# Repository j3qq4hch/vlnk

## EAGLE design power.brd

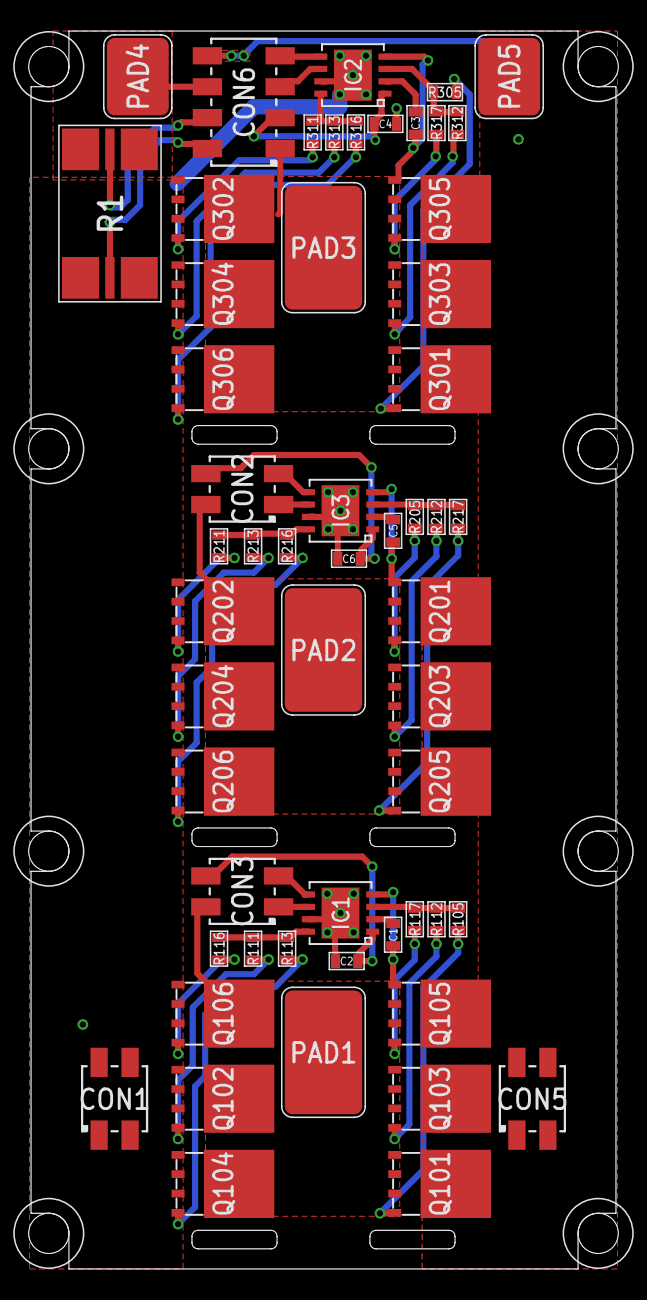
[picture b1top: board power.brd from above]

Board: 2 copper layers, 37.8 x 80.0 mm, 56 parts (0 on the bottom side), 42 nets.

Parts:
C1, C2, C3, C4, C5, C6: 0.1uF; C0603
CON1, CON2, CON3, CON5: PINHEAD_2X02-0877590414; 2X02-SMD-2-MALE
CON6: PINHEAD_2X04-SMD-2-MALE; 2X04-SMD-2-MALE
IC1, IC2, IC3: UCC272-VDFN-HEAVY_PCB; VDFN-8-HEAVY-PCB
PAD1, PAD2, PAD3: PAD-5X8; 5X8
PAD4, PAD5: PAD-5X4; 5X4
Q101, Q102, Q103, Q104, Q105, Q106, Q201, Q202, Q203, Q204, Q205, Q206, Q301, Q302, Q303, Q304, Q305, Q306: BSC077N12NS3GATMA1; PG-TDSON-8-1
R1: 500 µOhms; R3920-KELVIN
R105, R111, R112, R113, R116, R117, R205, R211, R212, R213, R216, R217, R305, R311, R312, R313, R316, R317: 4R3; R0603

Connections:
A_GH: IC1.3, R105.1, R112.1, R117.1
A_GL: IC1.8, R111.1, R113.1, R116.1
A_IH: CON3.3, IC1.5
A_IL: CON3.1, IC1.6
A_PH: C1.2, CON3.2, IC1.4, PAD1.P$1, Q101.1, Q101.2, Q101.3, Q102.P$1, Q103.1, Q103.2, Q103.3, Q104.P$1, Q105.1, Q105.2, Q105.3, Q106.P$1
B_GH: IC3.3, R205.1, R212.1, R217.1
B_GL: IC3.8, R211.1, R213.1, R216.1
B_IH: CON2.3, IC3.5
B_IL: CON2.1, IC3.6
B_PH: C5.2, CON2.2, IC3.4, PAD2.P$1, Q201.1, Q201.2, Q201.3, Q202.P$1, Q203.1, Q203.2, Q203.3, Q204.P$1, Q205.1, Q205.2, Q205.3, Q206.P$1
CS+: CON6.2, R1.S2
CS-: CON6.4, R1.S1
C_GH: IC2.3, R305.1, R312.1, R317.1
C_GL: IC2.8, R311.1, R313.1, R316.1
C_IH: CON6.7, IC2.5
C_IL: CON6.5, IC2.6
C_PH: C3.2, CON6.1, IC2.4, PAD3.P$1, Q301.1, Q301.2, Q301.3, Q302.P$1, Q303.1, Q303.2, Q303.3, Q304.P$1, Q305.1, Q305.2, Q305.3, Q306.P$1
unnamed: C3.1, IC2.2
unnamed: C5.1, IC3.2
unnamed: C1.1, IC1.2
PGND: C2.2, C4.2, C6.2, CON1.1, CON1.2, CON1.3, CON1.4, IC1.7, IC1.P$1, IC2.7, IC2.P$1, IC3.7, IC3.P$1, Q102.1, Q102.2, Q102.3, Q104.1, Q104.2, Q104.3, Q106.1, Q106.2, Q106.3, Q202.1, Q202.2, Q202.3, Q204.1, Q204.2, Q204.3, Q206.1, Q206.2, Q206.3, Q302.1, Q302.2, Q302.3, Q304.1, Q304.2, Q304.3, Q306.1, Q306.2, Q306.3, R1.2, R1.22
PHASE_A:N$1: Q101.4, R105.2
PHASE_A:N$2: Q102.4, R111.2
PHASE_A:N$3: Q103.4, R112.2
PHASE_A:N$4: Q104.4, R113.2
PHASE_A:N$5: Q105.4, R117.2
PHASE_A:N$6: Q106.4, R116.2
PHASE_B:N$1: Q201.4, R205.2
PHASE_B:N$2: Q202.4, R211.2
PHASE_B:N$3: Q203.4, R212.2
PHASE_B:N$4: Q204.4, R213.2
PHASE_B:N$5: Q205.4, R217.2
PHASE_B:N$6: Q206.4, R216.2
PHASE_C:N$1: Q301.4, R305.2
PHASE_C:N$2: Q302.4, R311.2
PHASE_C:N$3: Q303.4, R312.2
PHASE_C:N$4: Q304.4, R313.2
PHASE_C:N$5: Q305.4, R317.2
PHASE_C:N$6: Q306.4, R316.2
VBAT-: CON6.6, PAD4.P$1, R1.1, R1.11
VDC: CON5.1, CON5.2, CON5.3, CON5.4, CON6.8, PAD5.P$1, Q101.P$1, Q103.P$1, Q105.P$1, Q201.P$1, Q203.P$1, Q205.P$1, Q301.P$1, Q303.P$1, Q305.P$1
VDD_15V: C2.1, C4.1, C6.1, CON2.4, CON3.4, CON6.3, IC1.1, IC2.1, IC3.1

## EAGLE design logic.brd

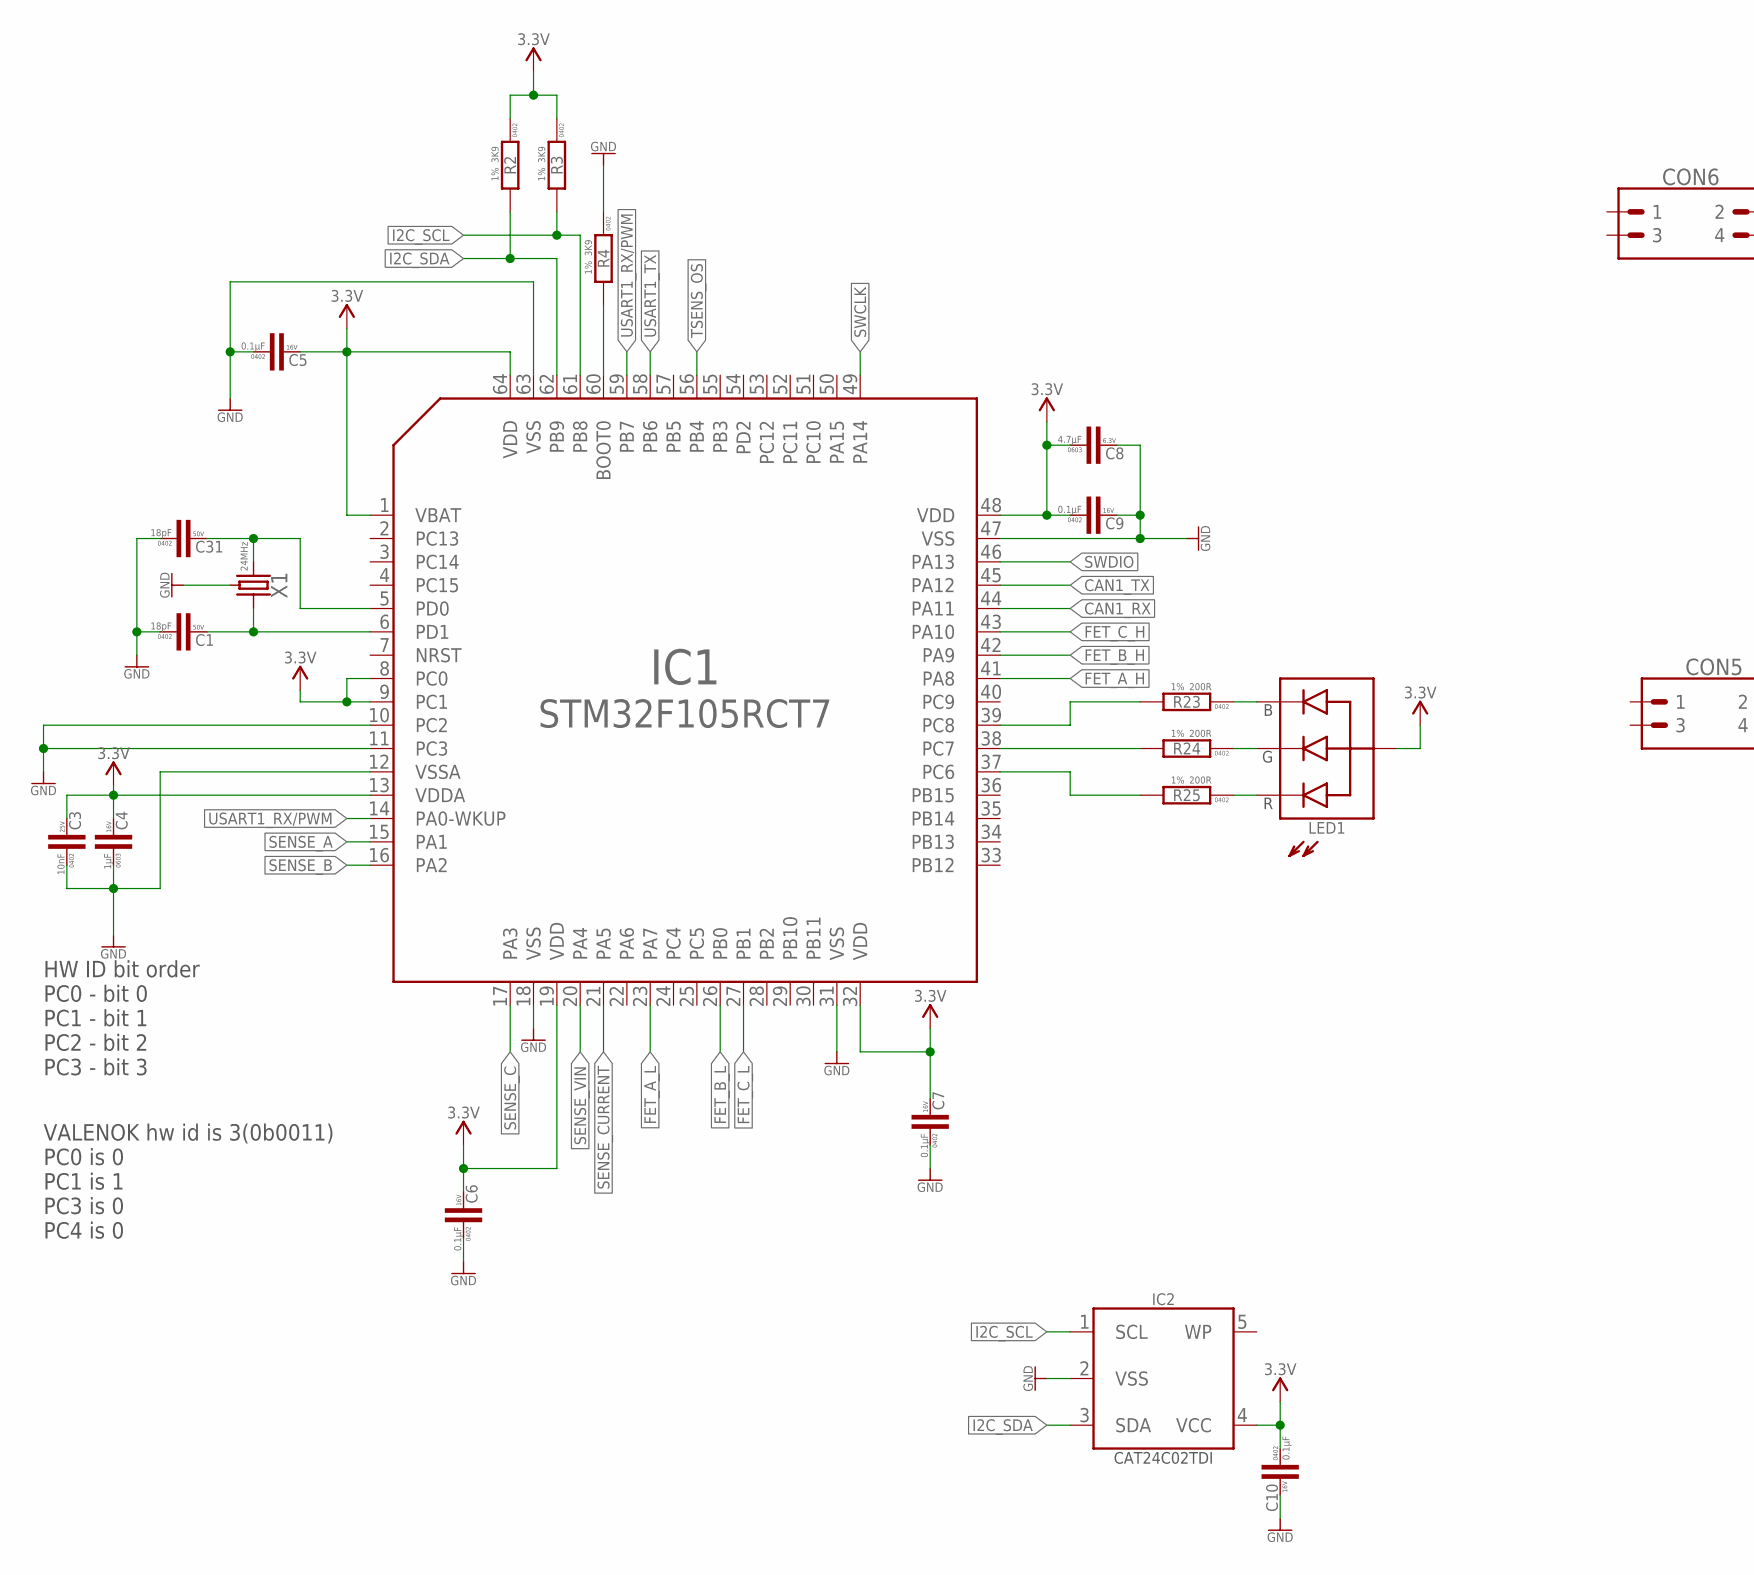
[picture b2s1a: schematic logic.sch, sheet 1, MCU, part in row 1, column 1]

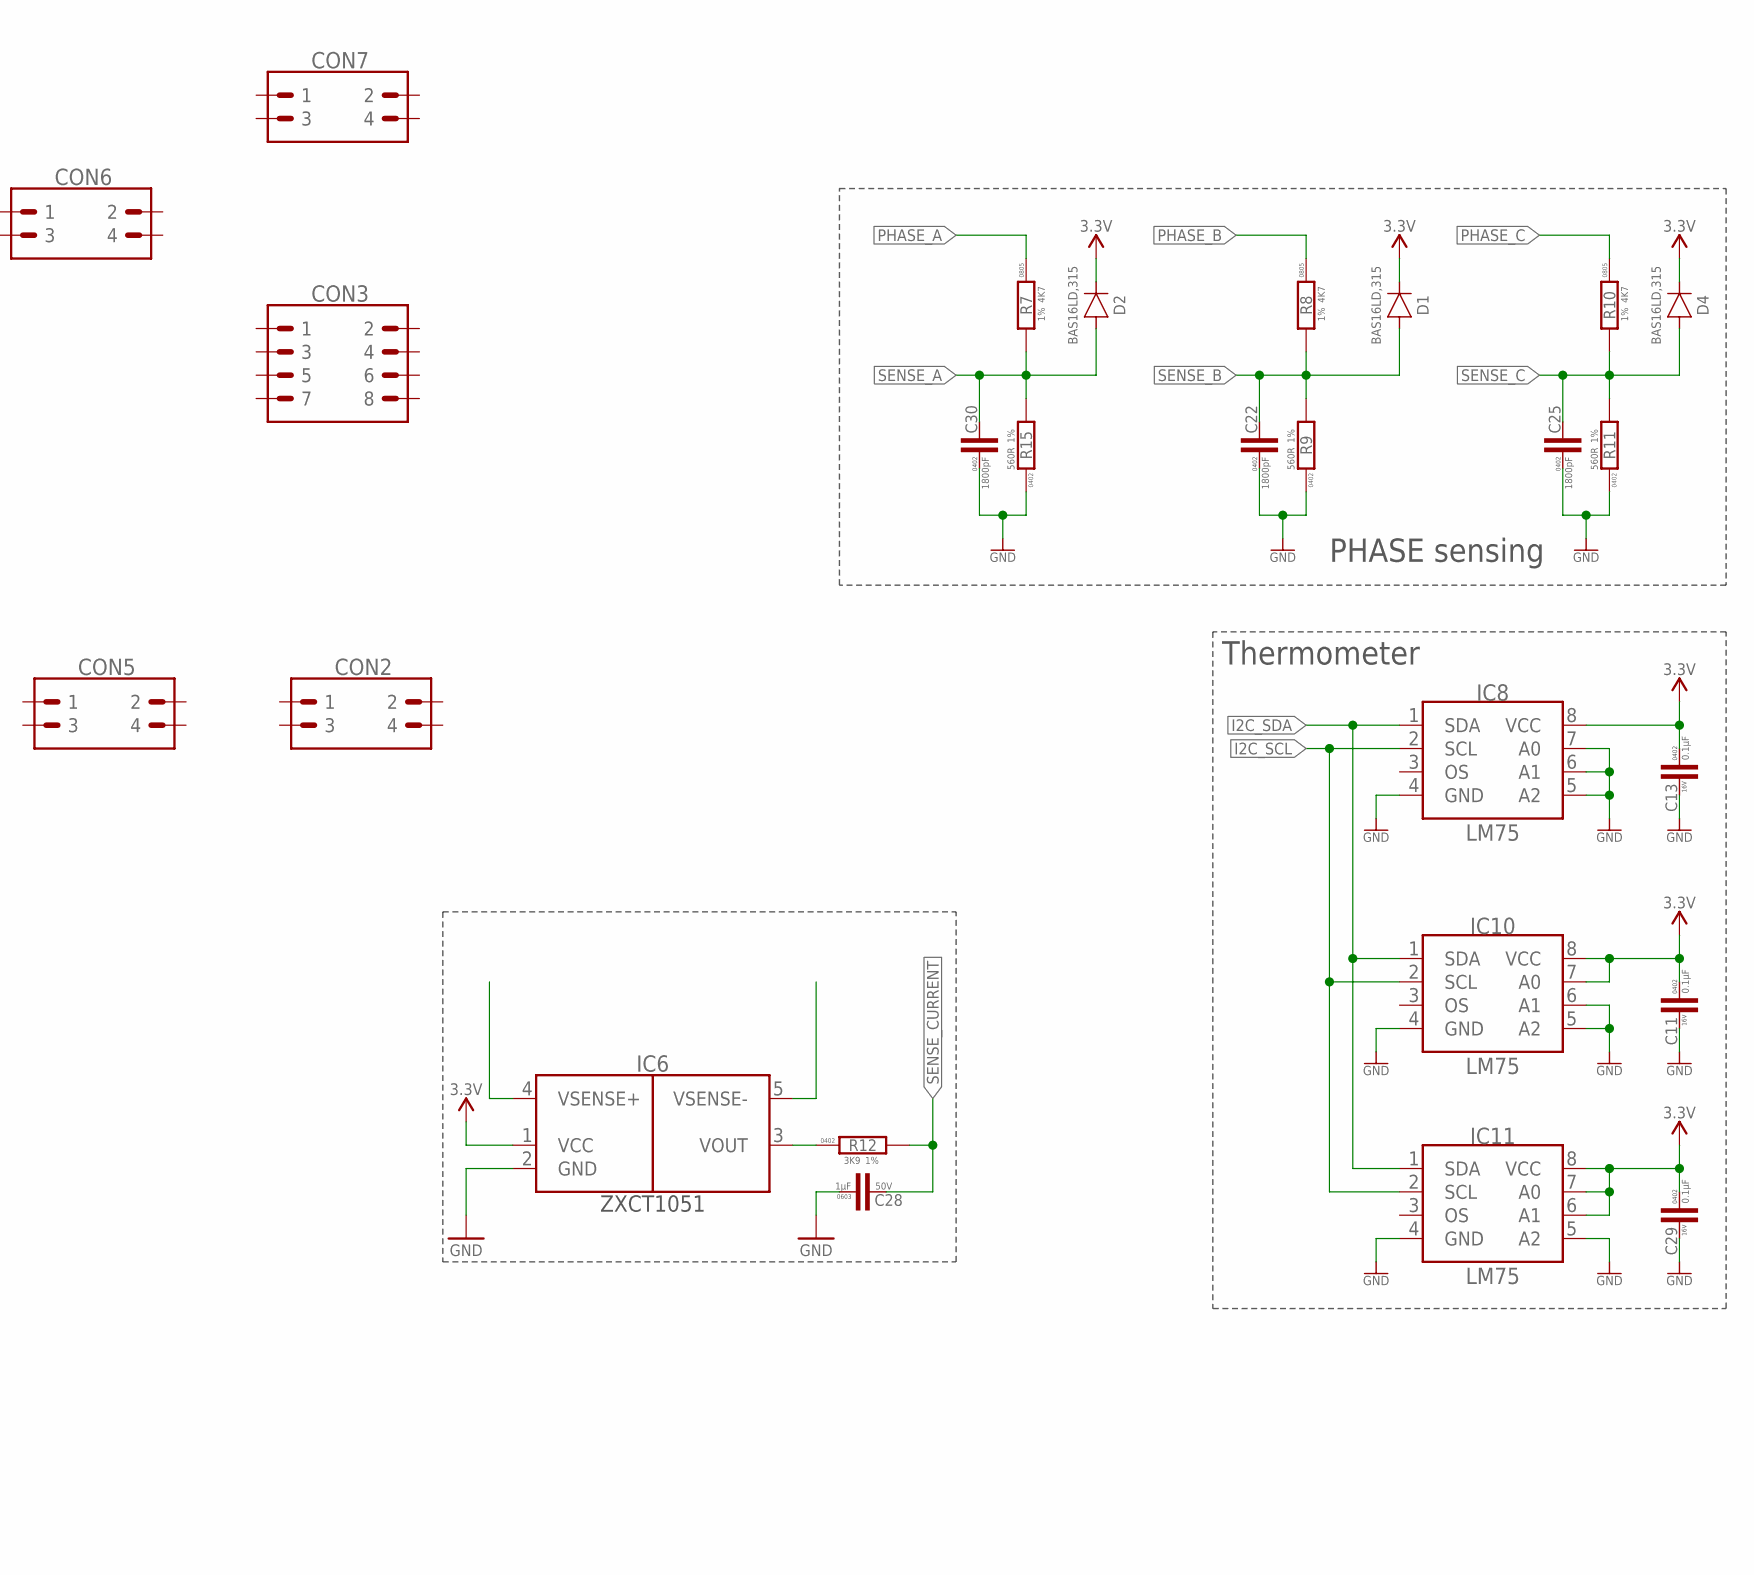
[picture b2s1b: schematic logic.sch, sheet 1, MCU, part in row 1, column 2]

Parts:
C1, C31: 18pF; C0402; VOLTAGE 50V; DIGIKEY# 399-8828-1-ND
C3: 10nF; C0402; VOLTAGE 25V; DIGIKEY# 490-6043-1-ND
C4: 1µF; C0603; VOLTAGE 16V; DIGIKEY# 445-12539-1-ND
C5, C6, C7, C9, C10, C11, C13, C29: 0.1µF; C0402; VOLTAGE 16V; DIGIKEY# 490-3261-1-ND
C8: 4.7µF; C0603; VOLTAGE 6.3V; DIGIKEY# 1276-2087-1-ND
C22, C25, C30: 1800pF; C0402
C28: 1µF; C0603
CON2, CON5, CON6, CON7: PINHEAD_2X02-PTH-2-MALE; 2X02-PTH-2
CON3: PINHEAD_2X04-PLS-2; 2X04-PTH-2
D1, D2, D4: BAS16L; SOD882
IC1: STM32F105RCT6; TQFP64; DIGIKEY# 497-11547-ND
IC2: CAT24C02; SOT23-5L@1
IC6: ZXCT1051; SOT23-5L
IC8, IC10, IC11: LM75-TSSOP8; TSSOP8
LED1: LTST-C19HE1WT; 0606
R2, R3, R4: 3K9; R0402; DIGIKEY# 311-3.90KLRCT-ND
R7, R8, R10: 4K7; R0805
R9, R11, R15: 560R; R0402
R12: 3K9; R0402
R23, R24, R25: 200R; R0402; DIGIKEY# 311-200JRCT-ND
X1: 24MHz; OSCILLATOR-3.2X2.5-4P; DIGIKEY# 1253-1198-1-ND

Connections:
BLABLA: IC6.3 (VOUT), R12.1
BOOT0: IC1.60 (BOOT0), R4.2
CAN1_RX: IC1.44 (PA11)
CAN1_TX: IC1.45 (PA12)
FET_A_H: IC1.41 (PA8)
FET_A_L: IC1.23 (PA7)
FET_B_H: IC1.42 (PA9)
FET_B_L: IC1.26 (PB0)
FET_C_H: IC1.43 (PA10)
FET_C_L: IC1.27 (PB1)
GND: C1.1, C3.1, C4.1, C5.1, C6.1, C7.1, C8.2, C9.2, C10.2, C11.2, C13.2, C22.1, C25.1, C28.P$1 (1), C29.2, C30.1, C31.1, IC1.10 (PC2), IC1.11 (PC3), IC1.12 (VSSA), IC1.18 (VSS), IC1.31 (VSS), IC1.47 (VSS), IC1.63 (VSS), IC2.2 (VSS), IC6.2 (GND), IC8.4 (GND), IC8.5 (A2), IC8.6 (A1), IC8.7 (A0), IC10.4 (GND), IC10.5 (A2), IC10.6 (A1), IC11.4 (GND), IC11.5 (A2), R4.1, R9.1, R11.1, R15.1, X1.2 (GND), X1.4 (GND); also elsewhere on the board
I2C_SCL: IC1.61 (PB8), IC2.1 (SCL), IC8.2 (SCL), IC10.2 (SCL), IC11.2 (SCL), R3.2
I2C_SDA: IC1.62 (PB9), IC2.3 (SDA), IC8.1 (SDA), IC10.1 (SDA), IC11.1 (SDA), R2.2
unnamed: IC1.37 (PC6), R25.2
unnamed: LED1.B, R23.1
unnamed: LED1.R, R25.1
unnamed: IC1.38 (PC7), R24.2
unnamed: C31.2, IC1.5 (PD0), X1.3 (2)
unnamed: IC1.39 (PC8), R23.2
unnamed: C1.2, IC1.6 (PD1), X1.1
unnamed: LED1.G, R24.1
PHASE_A: R7.1
PHASE_B: R8.1
PHASE_C: R10.1
SENSE_A: C30.2, D2.A, IC1.15 (PA1), R7.2, R15.2
SENSE_B: C22.2, D1.A, IC1.16 (PA2), R8.2, R9.2
SENSE_C: C25.2, D4.A, IC1.17 (PA3), R10.2, R11.2
SENSE_CURRENT: C28.P$2 (2), IC1.21 (PA5), R12.2
SENSE_VIN: IC1.20 (PA4)
SWCLK: IC1.49 (PA14)
SWDIO: IC1.46 (PA13)
TSENS_OS: IC1.56 (PB4)
USART1_RX/PWM: IC1.14 (PA0-WKUP), IC1.59 (PB7); also elsewhere on the board
USART1_TX: IC1.58 (PB6); also elsewhere on the board
VDD_3V3: C3.2, C4.2, C5.2, C6.2, C7.2, C8.1, C9.1, C10.1, C11.1, C13.1, C29.1, D1.C, D2.C, D4.C, IC1.1 (VBAT), IC1.8 (PC0), IC1.9 (PC1), IC1.13 (VDDA), IC1.19 (VDD), IC1.32 (VDD), IC1.48 (VDD), IC1.64 (VDD), IC2.4 (VCC), IC6.1 (VCC), IC8.8 (VCC), IC10.7 (A0), IC10.8 (VCC), IC11.6 (A1), IC11.7 (A0), IC11.8 (VCC), LED1.+ (A), R2.1, R3.1; also elsewhere on the board

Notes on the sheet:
Thermometer
HW ID bit order PC0 - bit 0 PC1 - bit 1 PC2 - bit 2 PC3 - bit 3
VALENOK hw id is 3(0b0011) PC0 is 0 PC1 is 1 PC3 is 0 PC4 is 0
PHASE sensing

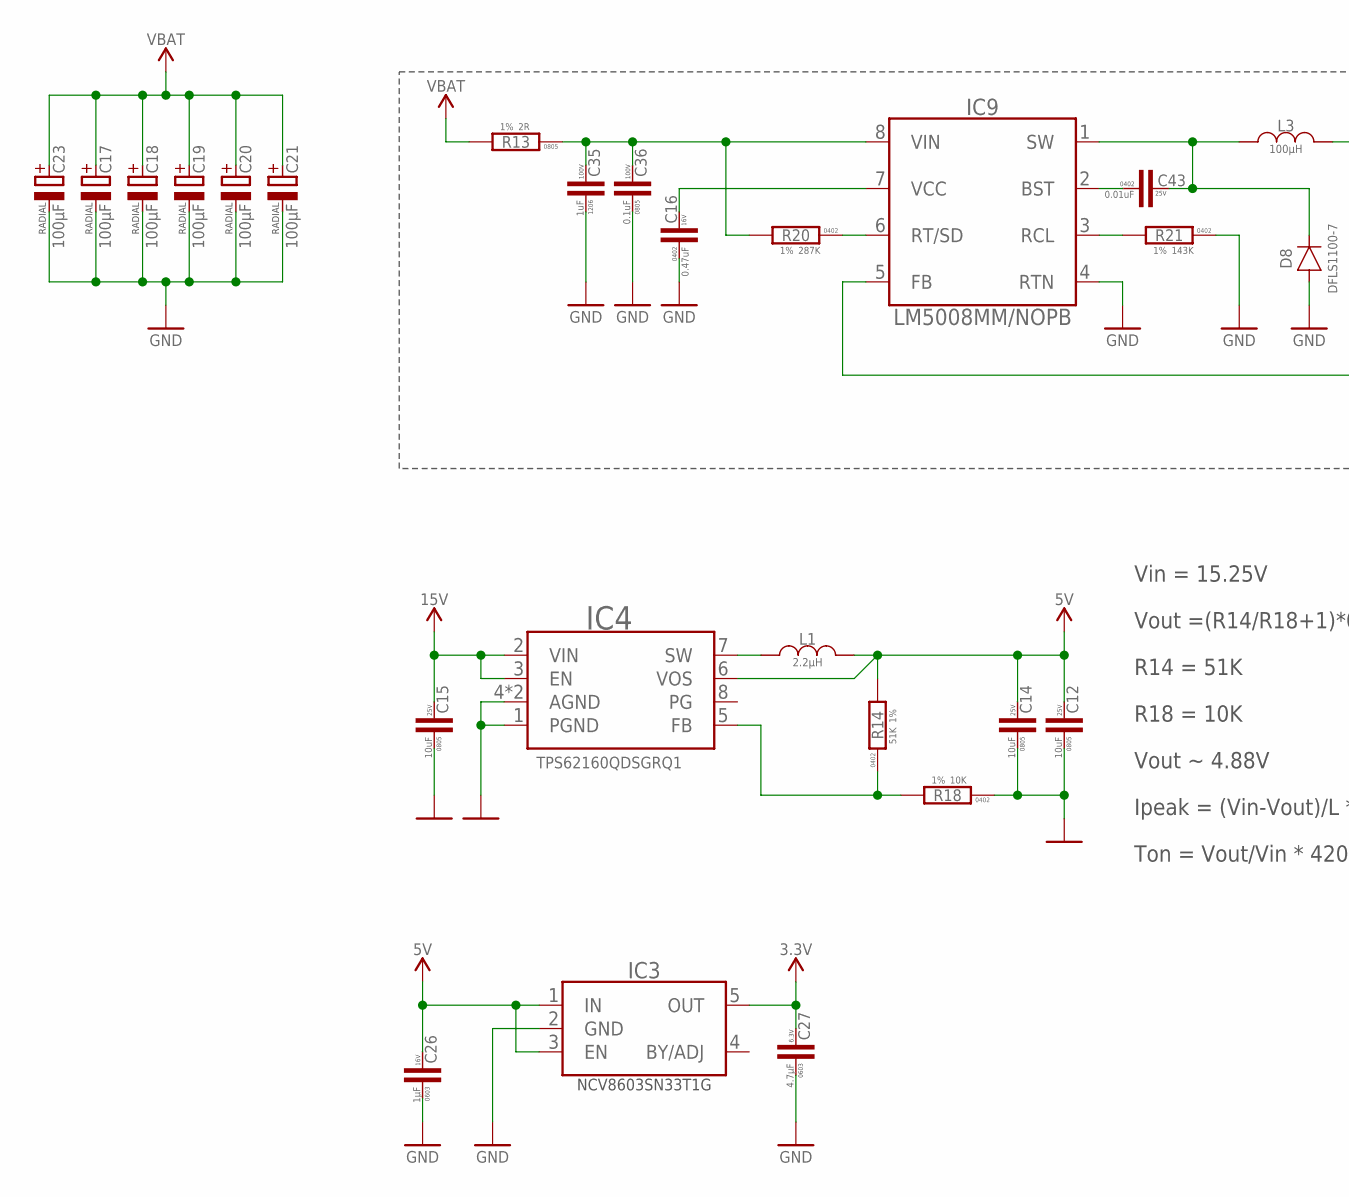
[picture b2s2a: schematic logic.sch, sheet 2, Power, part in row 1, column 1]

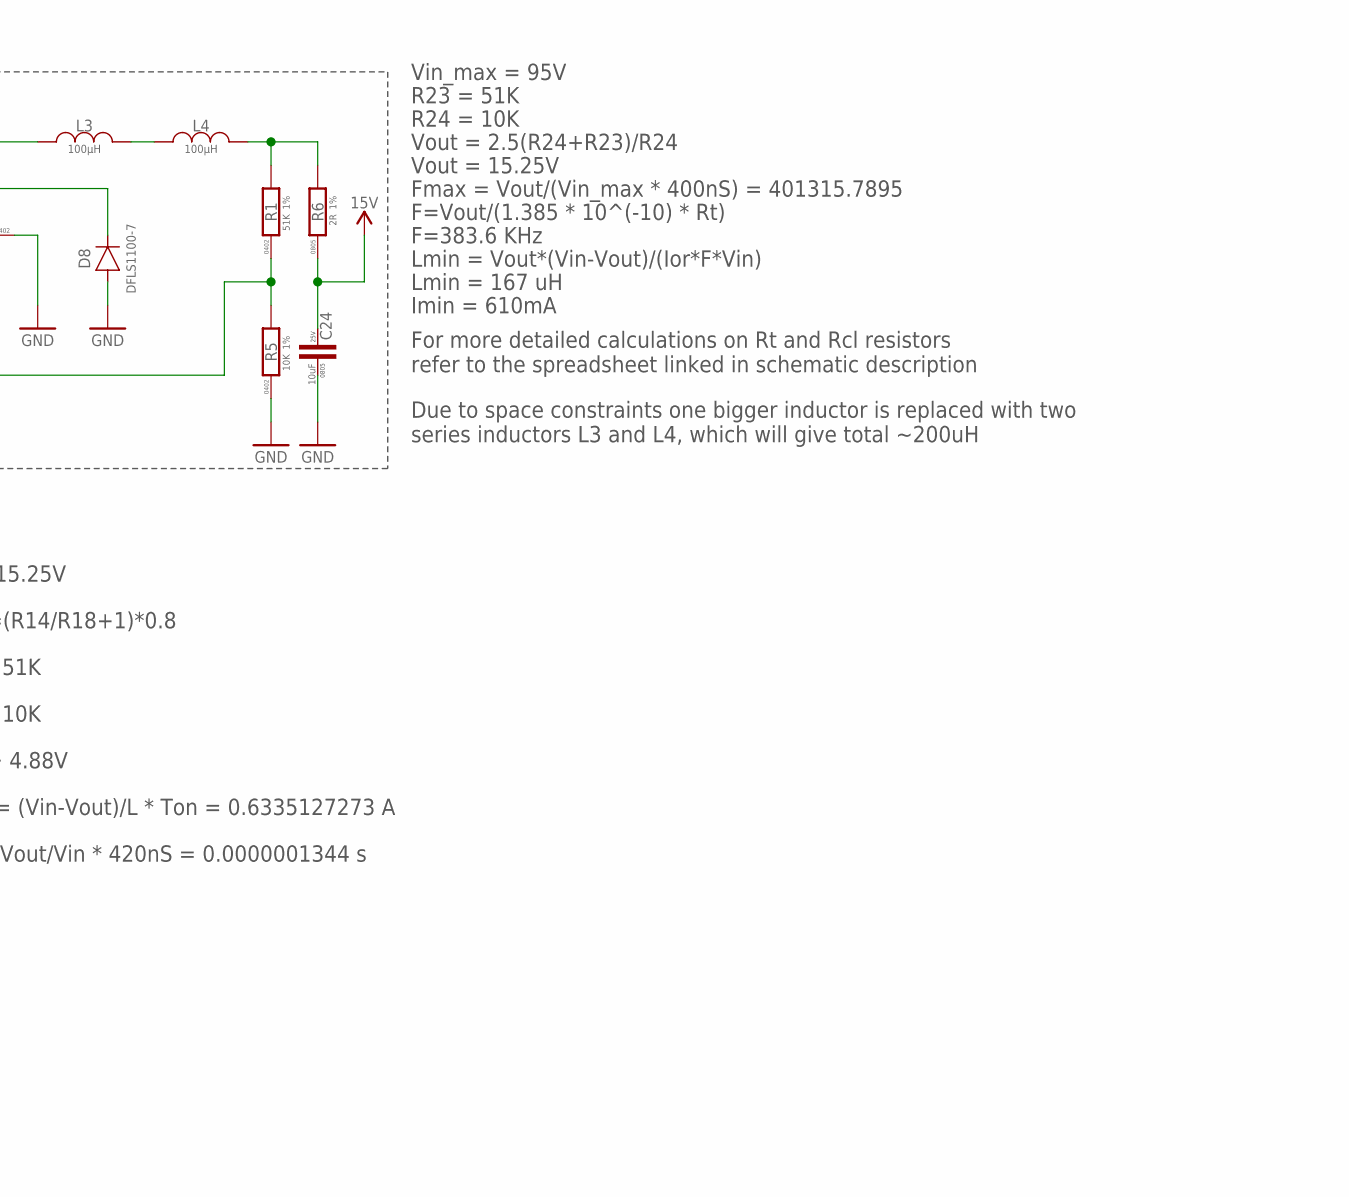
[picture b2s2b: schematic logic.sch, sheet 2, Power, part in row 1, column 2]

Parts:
C12, C14, C15, C24: 10uF; C0805; VOLTAGE 25V; DIGIKEY# 445-181411-1-ND
C16: 0.47uF; C0402; VOLTAGE 16V; DIGIKEY# 490-12244-1-ND
C17, C18, C19, C20, C21, C23: 100µF; RADIAL_SIDE_12.5X22; VOLTAGE 160V; DIGIKEY# 493-4784-3-ND
C26: 1µF; C0603; VOLTAGE 16V; DIGIKEY# 445-12539-1-ND
C27: 4.7µF; C0603; VOLTAGE 6.3V; DIGIKEY# 1276-2087-1-ND
C35: 1uF; C1206; VOLTAGE 100V; DIGIKEY# 490-16468-1-ND
C36: 0.1uF; C0805; VOLTAGE 100V; DIGIKEY# 445-5827-1-ND
C43: 0.01uF; C0402; VOLTAGE 25V; DIGIKEY# 490-6043-1-ND
D8: DFLS1100; POWERDI-123
IC3: NCV8603SN33; SOT23-5
IC4: TPS62160QDSGRQ1; WFDFN-8; DIGIKEY# 296-40840-1-ND
IC9: LM5008-MSOP8; MSOP8
L1: 2.2µH; NR3015
L3, L4: 100µH; LQS-6028
R1, R14: 51K; R0402; DIGIKEY# P51.0KLCT-ND
R5, R18: 10K; R0402; DIGIKEY# P10.0KLCT-ND
R6, R13: 2R; R0805; DIGIKEY# RMCF0805FT2R00CT-ND
R20: 287K; R0402; DIGIKEY# P287KLCT-ND
R21: 143K; R0402; DIGIKEY# P122734CT-ND

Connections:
GND: C12.1, C14.1, C15.1, C16.1, C17.-, C18.-, C19.-, C20.-, C21.-, C23.-, C24.1, C26.1, C27.1, C35.P$1 (1), C36.1, D8.A, IC3.2 (GND), IC4.1 (PGND), IC4.4 (AGND), IC4.EP (AGND), IC9.4 (RTN), R5.1, R18.1, R21.1; also elsewhere on the board
unnamed: IC4.7 (SW), L1.1
unnamed: C16.2, IC9.7 (VCC)
unnamed: IC9.6 (RT/SD), R20.1
unnamed: IC4.5 (FB), R14.1, R18.2
unnamed: C35.P$2 (2), C36.2, IC9.8 (VIN), R13.1, R20.2
unnamed: C43.1, IC9.2 (BST)
unnamed: IC9.3 (RCL), R21.2
unnamed: C43.2, D8.C, IC9.1 (SW), L3.P$1 (1)
unnamed: L4.P$2 (2), R1.2, R6.2
unnamed: L3.P$2 (2), L4.P$1 (1)
unnamed: IC9.5 (FB), R1.1, R5.2
VBAT: C17.+, C18.+, C19.+, C20.+, C21.+, C23.+, R13.2
VDD_3V3: C27.2, IC3.5 (OUT); also elsewhere on the board
VDD_5V: C12.2, C14.2, C26.2, IC3.1 (IN), IC3.3 (EN), IC4.6 (VOS), L1.2, R14.2
VDD_15V: C15.2, C24.2, IC4.2 (VIN), IC4.3 (EN), R6.1

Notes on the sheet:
Vout =(R14/R18+1)*0.8
Vin = 15.25V
R14 = 51K
R18 = 10K
Vout ~ 4.88V
Ipeak = (Vin-Vout)/L * Ton = 0.6335127273 A
Ton = Vout/Vin * 420nS = 0.0000001344 s
Vout = 2.5(R24+R23)/R24
Vin_max = 95V
R23 = 51K
R24 = 10K
Fmax = Vout/(Vin_max * 400nS) = 401315.7895
Vout = 15.25V
F=Vout/(1.385 * 10^(-10) * Rt)
F=383.6 KHz
Lmin = Vout*(Vin-Vout)/(Ior*F*Vin)
Lmin = 167 uH
Imin = 610mA
Due to space constraints one bigger inductor is replaced with two series inductors L3 and L4, which will give total ~200uH
For more detailed calculations on Rt and Rcl resistors refer to the spreadsheet linked in schematic description

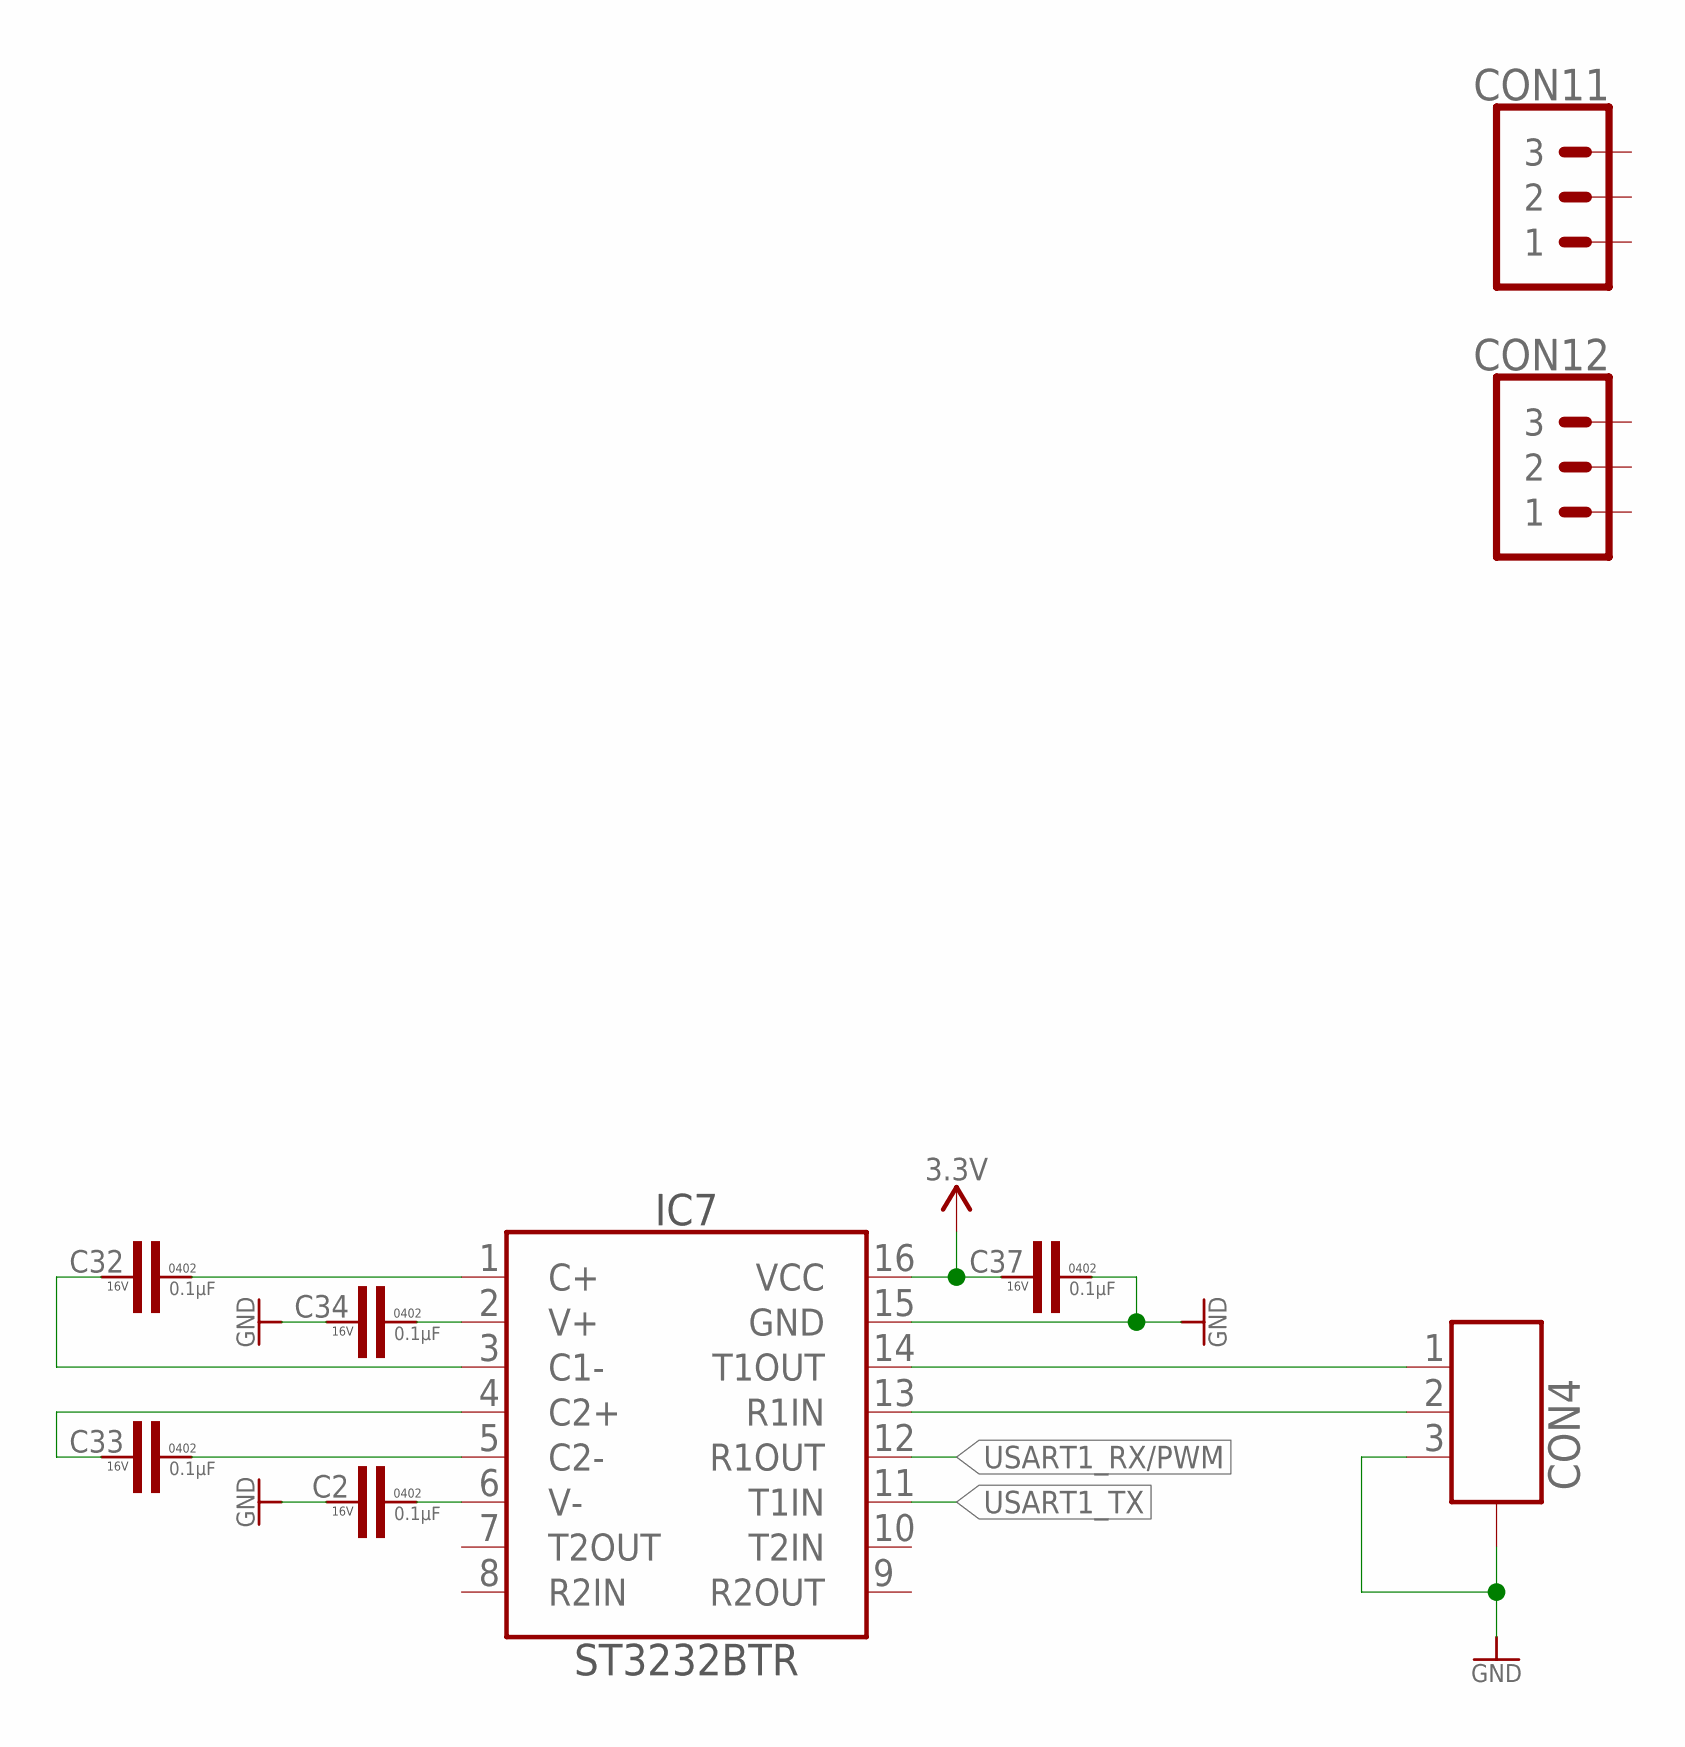
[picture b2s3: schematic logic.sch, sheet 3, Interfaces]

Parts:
C2, C32, C33, C34, C37: 0.1µF; C0402; VOLTAGE 16V; DIGIKEY# 490-3261-1-ND
CON4: CON-3P-TABS; JST_GH-3P-RA
CON11, CON12: PINHEAD_1X03-2; 1X03-PTH-2
IC7: ST3232; TSSOP16

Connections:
GND: C2.2, C34.2, C37.1, CON4.3, CON4.M$0 (GND), CON4.M$1 (GND), IC7.15 (GND); also elsewhere on the board
unnamed: C32.1, IC7.1 (C+)
unnamed: C32.2, IC7.3 (C1-)
unnamed: C33.1, IC7.5 (C2-)
unnamed: C33.2, IC7.4 (C2+)
unnamed: C2.1, IC7.6 (V-)
unnamed: C34.1, IC7.2 (V+)
unnamed: CON4.2, IC7.13 (R1IN)
unnamed: CON4.1, IC7.14 (T1OUT)
USART1_RX/PWM: IC7.12 (R1OUT); also elsewhere on the board
USART1_TX: IC7.11 (T1IN); also elsewhere on the board
VDD_3V3: C37.2, IC7.16 (VCC); also elsewhere on the board

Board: 4 copper layers, 86 parts (3 on the bottom side), 42 nets, no tracks yet.

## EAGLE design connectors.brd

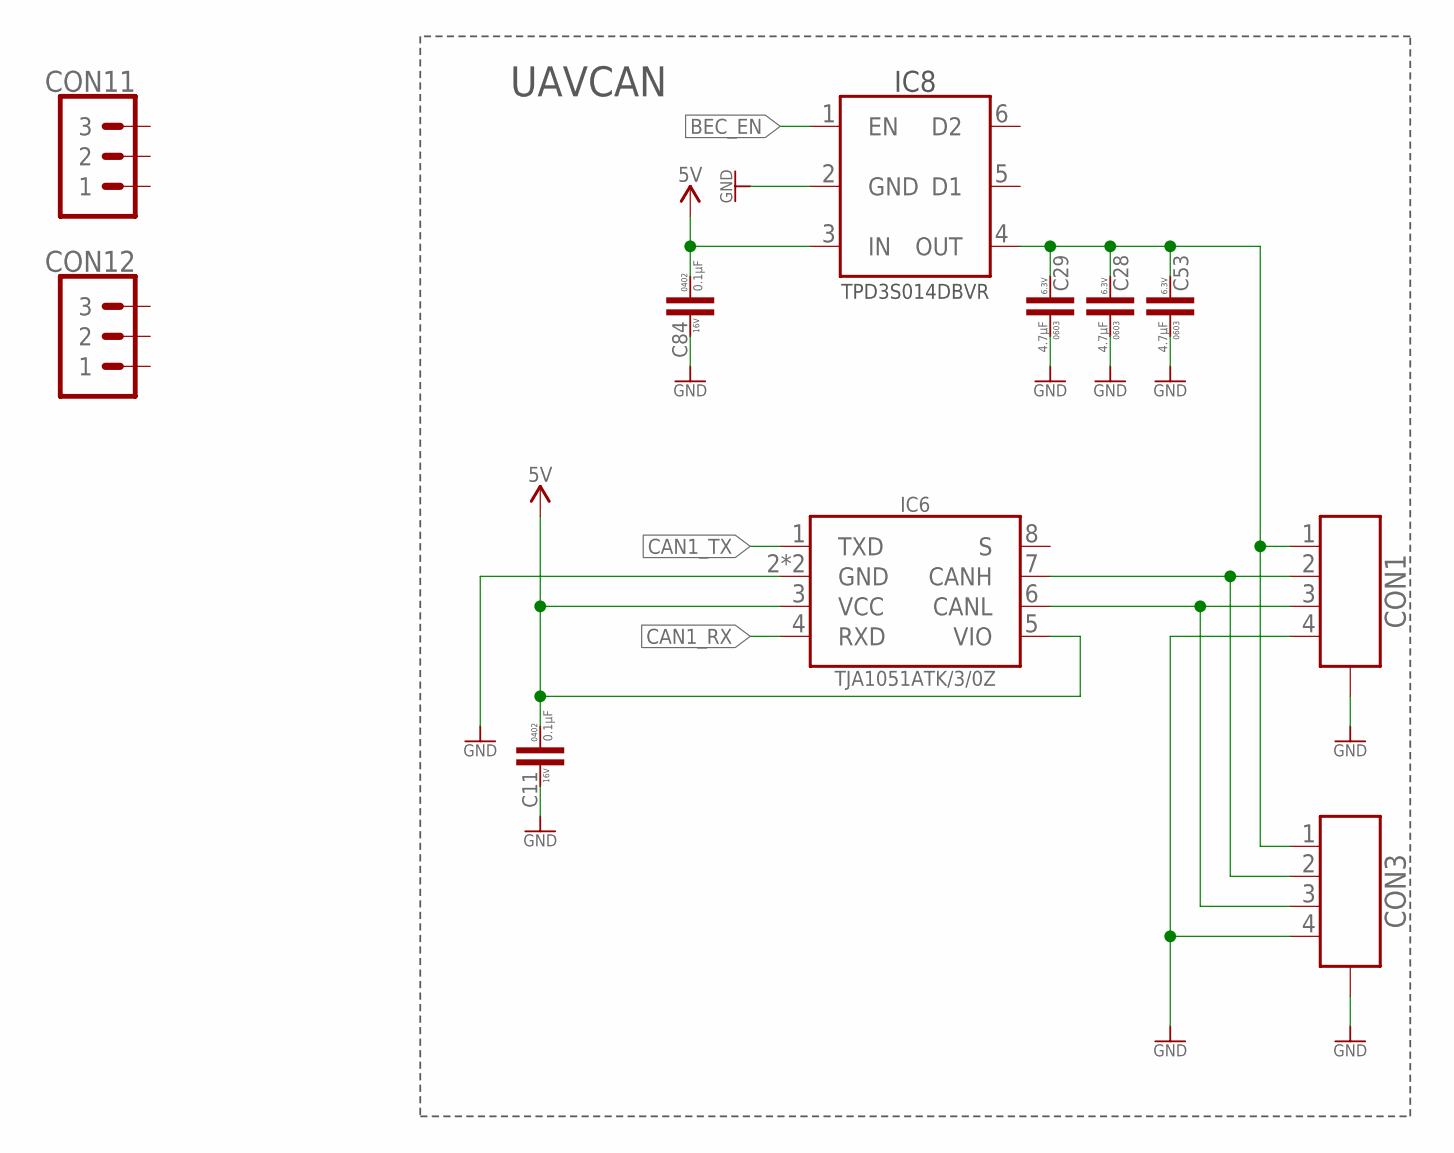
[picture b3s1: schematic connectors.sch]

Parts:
C11, C84: 0.1µF; C0402; VOLTAGE 16V; DIGIKEY# 490-3261-1-ND
C28, C29, C53: 4.7µF; C0603; VOLTAGE 6.3V; DIGIKEY# 1276-2087-1-ND
CON1, CON3: CON-4P-TABS-JST_GH-RA; JST_GH-4P-RA
CON11, CON12: PINHEAD_1X03-2; 1X03-PTH-2
IC6: TJA1051-HVSON8; SOT782-1
IC8: TPD3S014DBVR-SOT23-6; SOT26

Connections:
BEC_EN: IC8.1 (EN)
CAN1_RX: IC6.4 (RXD)
CAN1_TX: IC6.1 (TXD)
CAN1_VDD: C28.2, C29.2, C53.2, CON1.1, CON3.1, IC8.4 (OUT)
GND: C11.2, C28.1, C29.1, C53.1, C84.2, CON1.4, CON1.M$0 (GND), CON1.M$1 (GND), CON3.4, CON3.M$0 (GND), CON3.M$1 (GND), IC6.2 (GND), IC6.PAD (GND), IC8.2 (GND)
unnamed: CON1.2, CON3.2, IC6.7 (CANH)
unnamed: CON1.3, CON3.3, IC6.6 (CANL)
VDD_5V: C11.1, C84.1, IC6.3 (VCC), IC6.5 (VIO), IC8.3 (IN)

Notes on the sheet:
UAVCAN

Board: 2 copper layers, 11 parts (0 on the bottom side), 5 nets, no tracks yet.

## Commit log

2020-10-07 initial import
2020-10-07 pwr pcb routing completed
2020-10-07 blah
